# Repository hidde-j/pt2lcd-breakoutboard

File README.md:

# pt2lcd-breakoutboard
Simple LPM015M135A breakout board 

#### Voltage regulator

The LPM015M135A expects 4.5V on VDDP, so an LT3009 voltage regulator is included in the design that steps 5V down to 4.5V.

#### Missing footprints/symbols

The BM20B-24DS and LT3009 footprints are not included due to copyright reasons. These can be found by searching for the part numbers on Digikey. These are the expected file locations:

```
.
├── BM20B-24DS
│   ├── 2024-12-25_12-01-17.kicad_sym
│   ├── BM20B(0.6)-24DS-0.4V(53).STEP
│   └── footprints.pretty
│       └── BM20B0.6-24DS-0.4V53_HIR.kicad_mod
├── LT3009
│   ├── 2024-12-23_21-50-19.kicad_sym
│   ├── 3009fd.pdf
│   └── footprints.pretty
│       ├── DFN-6_DC_LIT.kicad_mod
│       ├── DFN-6_DC_LIT-L.kicad_mod
│       └── DFN-6_DC_LIT-M.kicad_mod
```

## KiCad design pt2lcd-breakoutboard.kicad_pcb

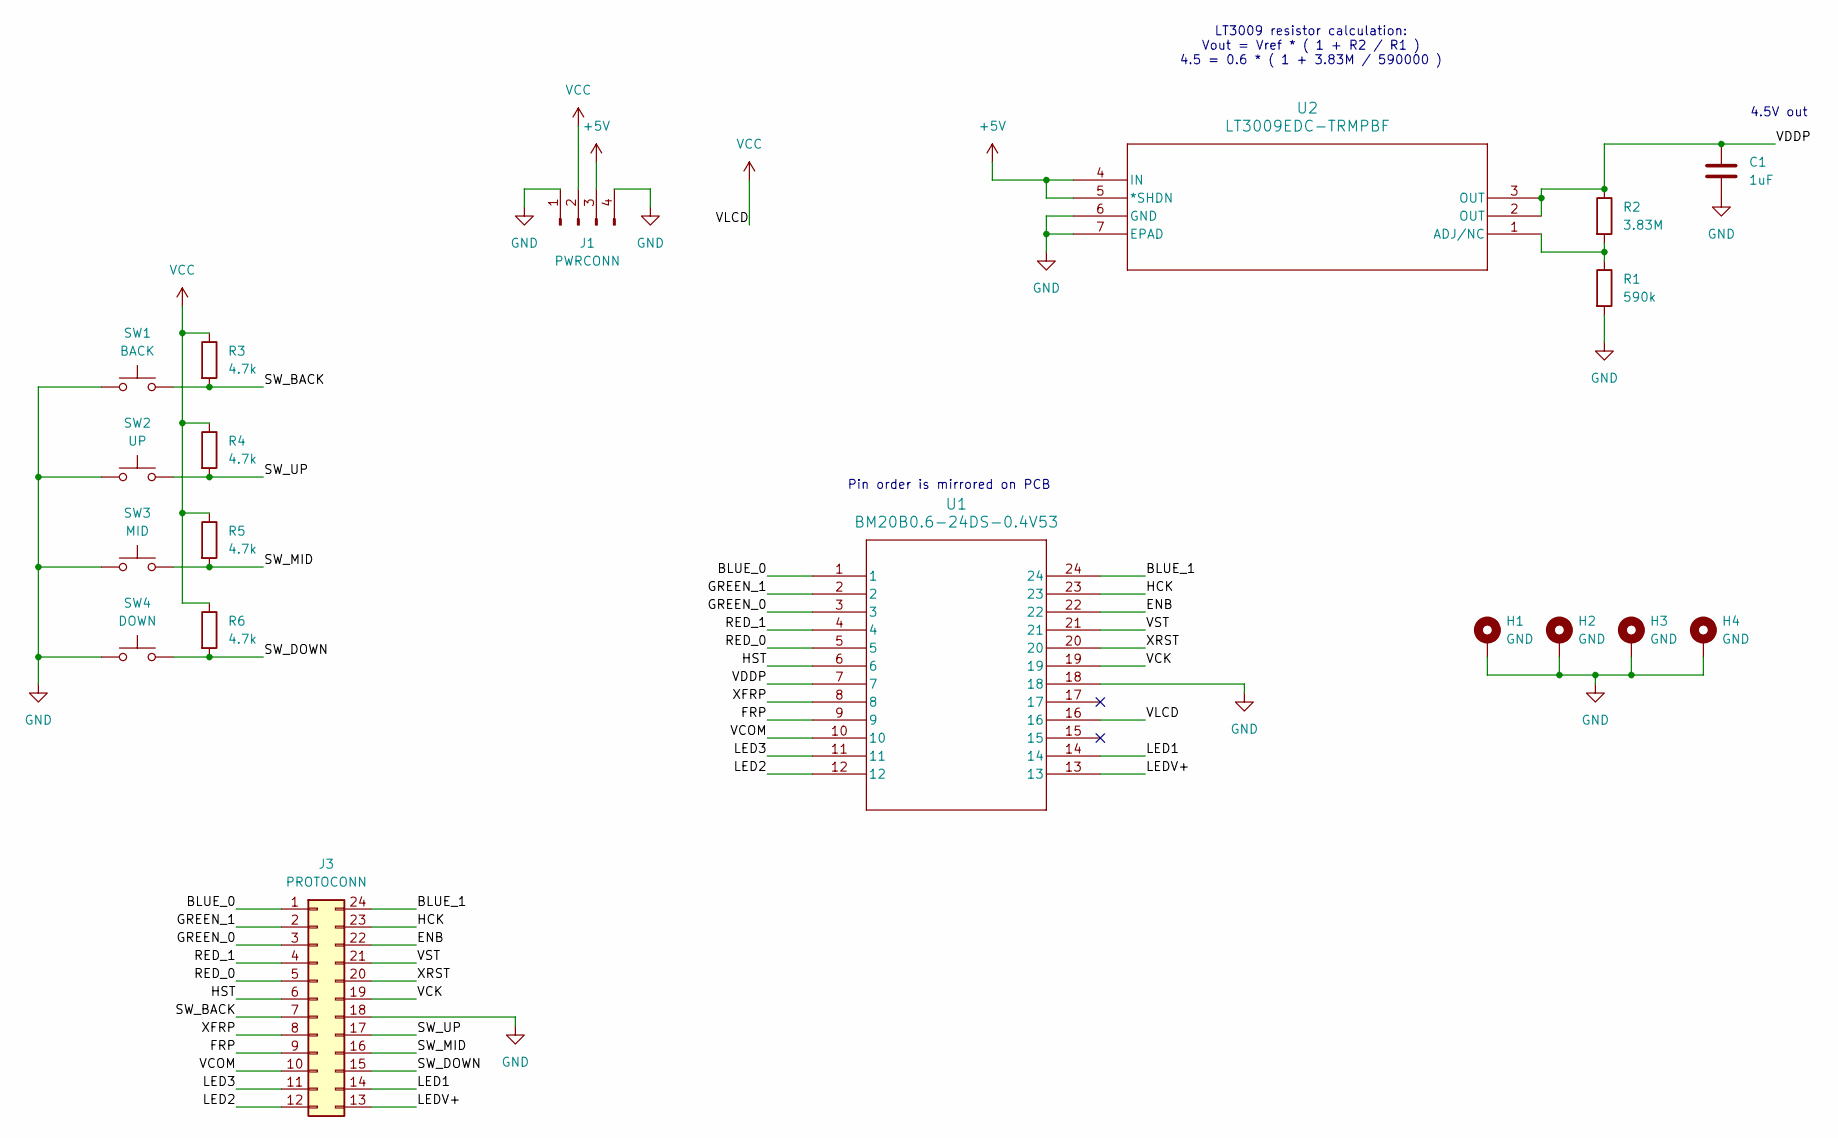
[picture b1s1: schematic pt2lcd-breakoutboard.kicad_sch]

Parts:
C1: 1uF; C_0603_1608Metric; LCSC C15849
H1, H2, H3, H4: GND; MountingHole_3.5mm_Pad
J1: PWRCONN; PinHeader_1x04_P2.54mm_Vertical
J3: PROTOCONN; PinHeader_2x12_P2.54mm_Vertical
R1: 590k; R_0603_1608Metric; LCSC C5126105
R2: 3.83M; R_0603_1608Metric; LCSC C482841
R3, R4, R5, R6: 4.7k; R_0603_1608Metric; LCSC C23162
SW1: BACK; SW_SPST_SKQG_WithStem
SW2: UP; SW_SPST_SKQG_WithStem
SW3: MID; SW_SPST_SKQG_WithStem
SW4: DOWN; SW_SPST_SKQG_WithStem
U1: BM20B0.6-24DS-0.4V53; BM20B0.6-24DS-0.4V53_HIR
U2: LT3009EDC-TRMPBF; DFN-6_DC_LIT; LCSC C666166

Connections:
+5V: J1.3, U2.4 (IN), U2.5 (*SHDN)
/BLUE_0: J3.1, U1.1
/BLUE_1: J3.24, U1.24
/ENB: J3.22, U1.22
/FRP: J3.9, U1.9
/GREEN_0: J3.3, U1.3
/GREEN_1: J3.2, U1.2
/HCK: J3.23, U1.23
/HST: J3.6, U1.6
/LED1: J3.14, U1.14
/LED2: J3.12, U1.12
/LED3: J3.11, U1.11
/LEDV+: J3.13, U1.13
/RED_0: J3.5, U1.5
/RED_1: J3.4, U1.4
/SW_BACK: J3.7, R3.2, SW1.2
/SW_DOWN: J3.15, R6.2, SW4.2
/SW_MID: J3.16, R5.2, SW3.2
/SW_UP: J3.17, R4.2, SW2.2
/VCK: J3.19, U1.19
/VCOM: J3.10, U1.10
/VDDP: C1.1, R2.1, U1.7, U2.2 (OUT), U2.3 (OUT)
/VST: J3.21, U1.21
/XFRP: J3.8, U1.8
/XRST: J3.20, U1.20
GND: C1.2, H1.1, H2.1, H3.1, H4.1, J1.1, J1.4, J3.18, R1.2, SW1.1, SW2.1, SW3.1, SW4.1, U1.18, U2.6 (GND), U2.7 (EPAD)
unnamed: R1.1, R2.2, U2.1 (ADJ/NC)
VCC: J1.2, R3.1, R4.1, R5.1, R6.1, U1.16

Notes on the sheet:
Pin order is mirrored on PCB
LT3009 resistor calculation: Vout = Vref * ( 1 + R2 / R1 ) 4.5 = 0.6 * ( 1 + 3.83M / 590000 )
4.5V out

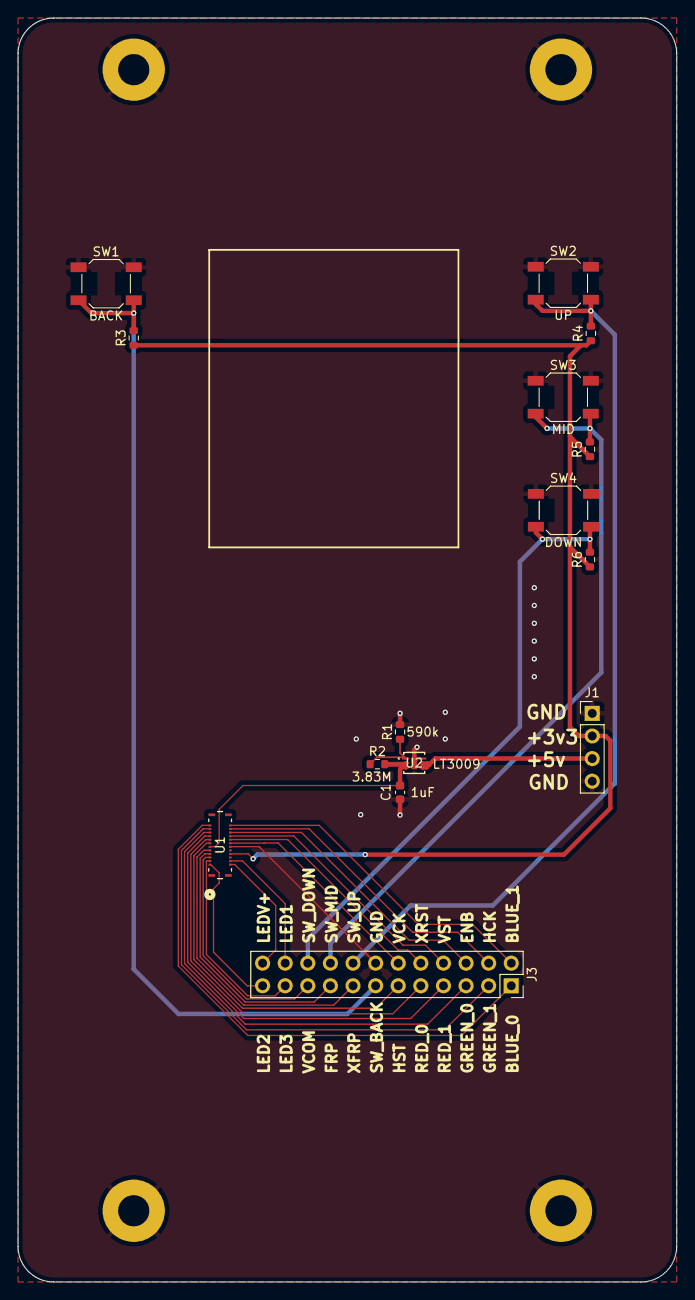
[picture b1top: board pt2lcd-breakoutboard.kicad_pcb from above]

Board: 2 copper layers, 74.0 x 142.0 mm, 19 parts (0 on the bottom side), 28 nets.

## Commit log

2025-05-16 add README.md
2025-05-19 changed trace spacing
